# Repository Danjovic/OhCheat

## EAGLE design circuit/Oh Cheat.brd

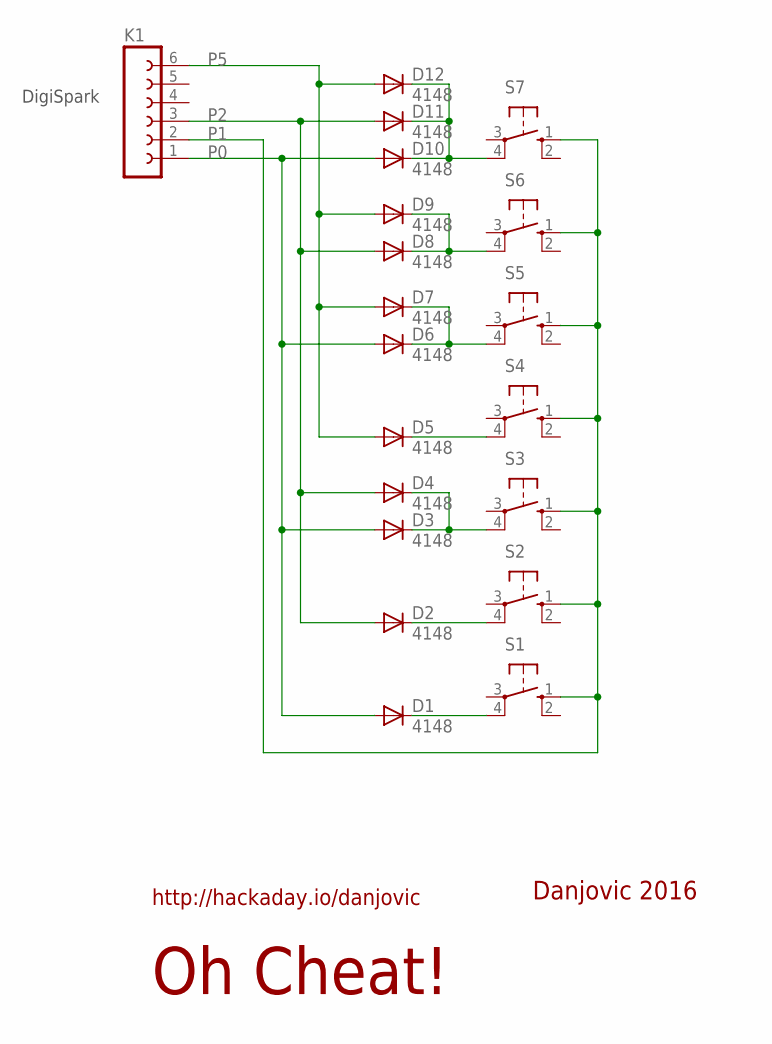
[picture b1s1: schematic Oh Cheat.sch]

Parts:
D1, D2, D3, D4, D5, D6, D7, D8, D9, D10, D11, D12: 4148; DO35-7
K1: FE06-1; FE06
S1, S2, S3, S4, S5, S6, S7: 40-XX; B3F-40XX

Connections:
unnamed: D10.C, D11.C, D12.C, S7.4 (P1)
unnamed: D8.C, D9.C, S6.4 (P1)
unnamed: D6.C, D7.C, S5.4 (P1)
unnamed: D5.C, S4.4 (P1)
unnamed: D3.C, D4.C, S3.4 (P1)
unnamed: D2.C, S2.4 (P1)
unnamed: D1.C, S1.4 (P1)
P0: D1.A, D3.A, D6.A, D10.A, K1.1
P1: K1.2, S1.1 (S), S2.1 (S), S3.1 (S), S4.1 (S), S5.1 (S), S6.1 (S), S7.1 (S)
P2: D2.A, D4.A, D8.A, D11.A, K1.3
P5: D5.A, D7.A, D9.A, D12.A, K1.6

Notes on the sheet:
Danjovic 2016
http://hackaday.io/danjovic
DigiSpark
Oh Cheat!

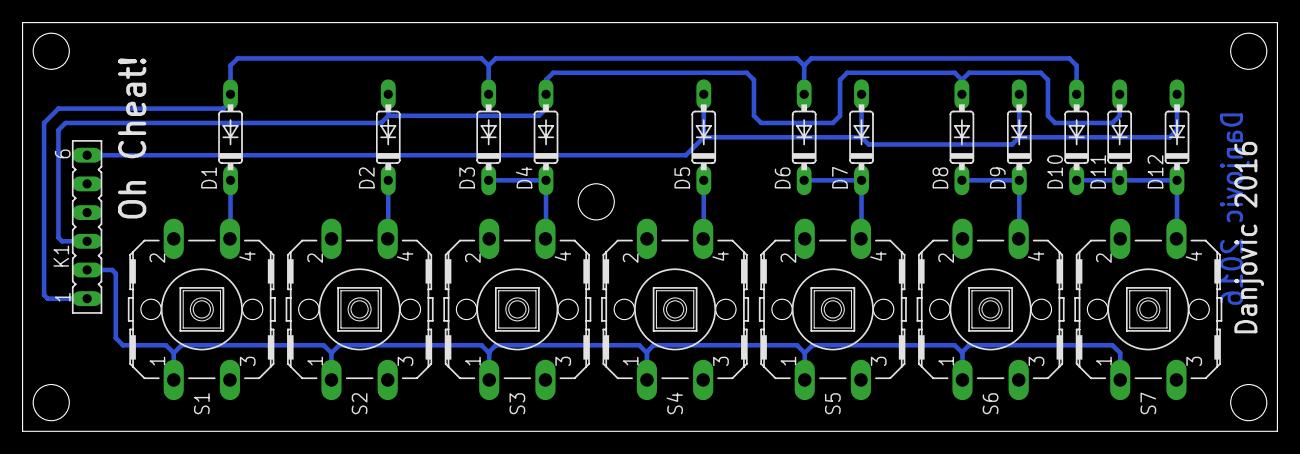
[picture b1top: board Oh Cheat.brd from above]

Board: 2 copper layers, 111.1 x 36.2 mm, 20 parts (0 on the bottom side), 11 nets.

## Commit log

2016-01-21 :space_invader: Added .gitattributes & .gitignore files
2016-01-21 Basic Release
2016-01-22 GTA bug corrected
    Created custom function for send keystrokes to the host as well as a new print function with the purpose of sustain the key press for a given time before releasing the key. For GTA this time shall be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
